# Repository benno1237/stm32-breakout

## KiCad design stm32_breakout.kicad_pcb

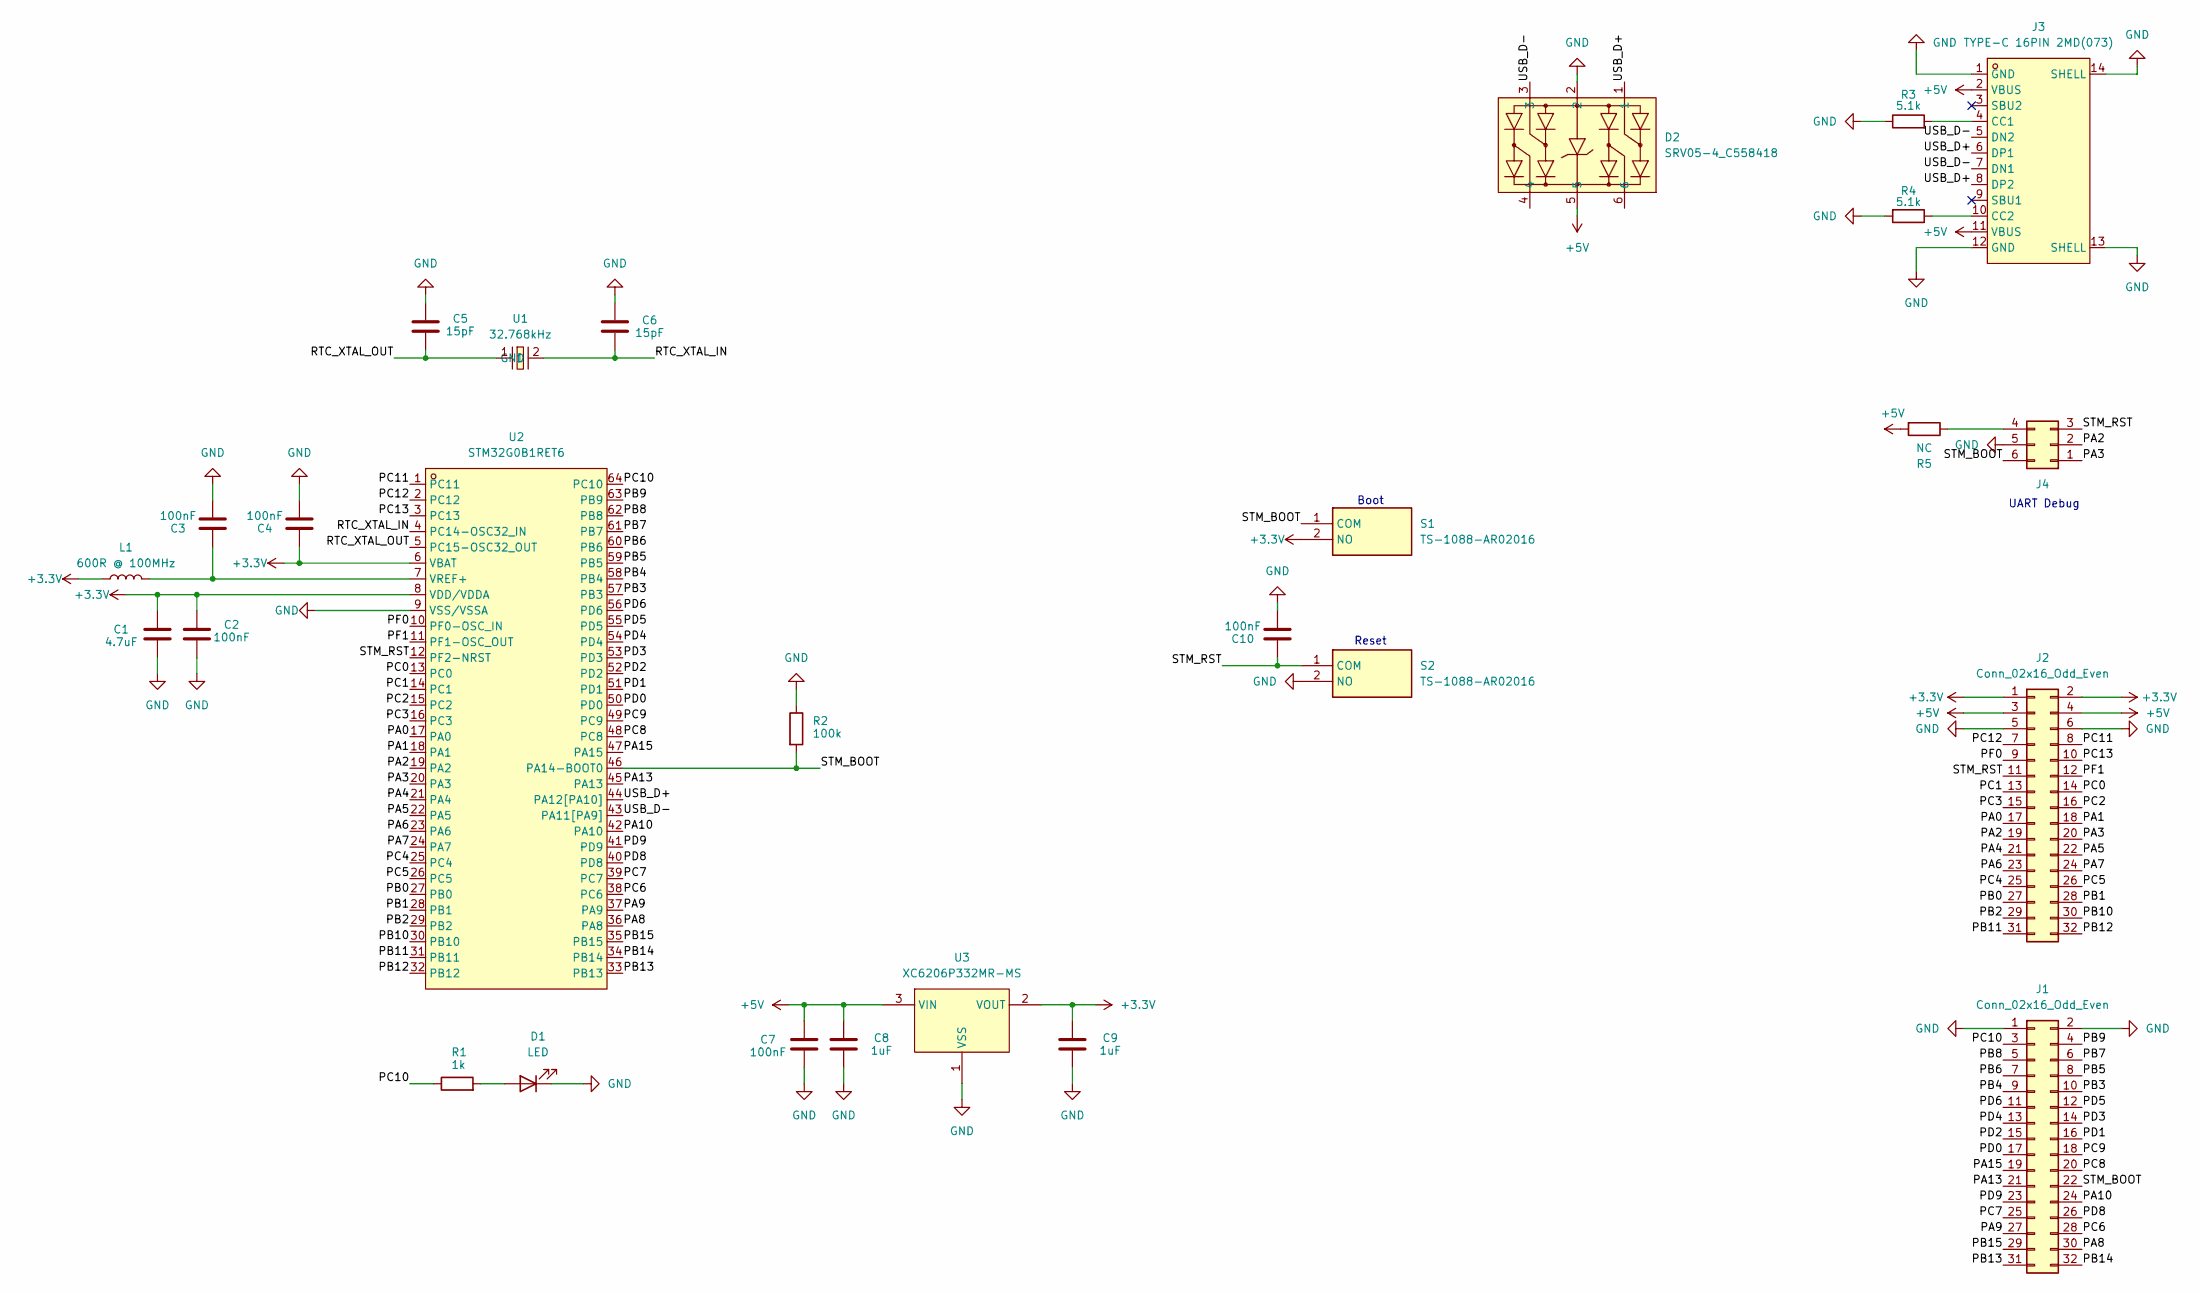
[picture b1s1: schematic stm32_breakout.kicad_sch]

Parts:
C1: 4.7uF; C_0603_1608Metric
C2, C3, C4, C7, C10: 100nF; C_0603_1608Metric
C5, C6: 15pF; C_0603_1608Metric
C8, C9: 1uF; C_0603_1608Metric
D1: LED; LED_0603_1608Metric
D2: SRV05-4_C558418; SOT-23-6_L2.9-W1.6-P0.95-LS2.8-BL; LCSC Part C558418
J1, J2: Conn_02x16_Odd_Even; PinHeader_2x16_P2.54mm_Vertical
J3: TYPE-C 16PIN 2MD(073); USB-C-SMD_TYPE-C-6PIN-2MD-073; LCSC Part C2765186
J4: PinSocket_2x03_P2.54mm_Vertical
L1: 600R @ 100MHz; L_0603_1608Metric
R1: 1k; R_0603_1608Metric
R2: 100k; R_0603_1608Metric
R3, R4: 5.1k; R_0603_1608Metric
R5: NC; R_0603_1608Metric
S1, S2: TS-1088-AR02016; SW-SMD_L3.9-W3.0-P4.45; Manufacturer_Part_Number TS-1088-AR02016
U1: 32.768kHz; CRYSTAL-SMD_L3.2-W1.5-1; LCSC Part C5361379
U2: STM32G0B1RET6; LQFP-64_L10.0-W10.0-P0.50-LS12.0-BL; LCSC Part C2829307
U3: XC6206P332MR-MS; SOT-23-3_L2.9-W1.3-P1.90-LS2.4-BR; LCSC Part C5252899

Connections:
+3.3V: C1.1, C2.1, C4.1, C9.2, J2.1, J2.2, L1.1, S1.2 (NO), U2.6 (VBAT), U2.8 (VDD/VDDA), U3.2 (VOUT)
+5V: C7.2, C8.2, D2.5, J2.3, J2.4, J3.2 (VBUS), J3.11 (VBUS), R5.2, U3.3 (VIN)
/PA0: J2.17, U2.17 (PA0)
/PA1: J2.18, U2.18 (PA1)
/PA2: J2.19, J4.2, U2.19 (PA2)
/PA3: J2.20, J4.1, U2.20 (PA3)
/PA4: J2.21, U2.21 (PA4)
/PA5: J2.22, U2.22 (PA5)
/PA6: J2.23, U2.23 (PA6)
/PA7: J2.24, U2.24 (PA7)
/PA8: J1.30, U2.36 (PA8)
/PA9: J1.27, U2.37 (PA9)
/PA10: J1.24, U2.42 (PA10)
/PA13: J1.21, U2.45 (PA13)
/PA15: J1.19, U2.47 (PA15)
/PB0: J2.27, U2.27 (PB0)
/PB1: J2.28, U2.28 (PB1)
/PB2: J2.29, U2.29 (PB2)
/PB3: J1.10, U2.57 (PB3)
/PB4: J1.9, U2.58 (PB4)
/PB5: J1.8, U2.59 (PB5)
/PB6: J1.7, U2.60 (PB6)
/PB7: J1.6, U2.61 (PB7)
/PB8: J1.5, U2.62 (PB8)
/PB9: J1.4, U2.63 (PB9)
/PB10: J2.30, U2.30 (PB10)
/PB11: J2.31, U2.31 (PB11)
/PB12: J2.32, U2.32 (PB12)
/PB13: J1.31, U2.33 (PB13)
/PB14: J1.32, U2.34 (PB14)
/PB15: J1.29, U2.35 (PB15)
/PC0: J2.14, U2.13 (PC0)
/PC1: J2.13, U2.14 (PC1)
/PC2: J2.16, U2.15 (PC2)
/PC3: J2.15, U2.16 (PC3)
/PC4: J2.25, U2.25 (PC4)
/PC5: J2.26, U2.26 (PC5)
/PC6: J1.28, U2.38 (PC6)
/PC7: J1.25, U2.39 (PC7)
/PC8: J1.20, U2.48 (PC8)
/PC9: J1.18, U2.49 (PC9)
/PC10: J1.3, R1.1, U2.64 (PC10)
/PC11: J2.8, U2.1 (PC11)
/PC12: J2.7, U2.2 (PC12)
/PC13: J2.10, U2.3 (PC13)
/PD0: J1.17, U2.50 (PD0)
/PD1: J1.16, U2.51 (PD1)
/PD2: J1.15, U2.52 (PD2)
/PD3: J1.14, U2.53 (PD3)
/PD4: J1.13, U2.54 (PD4)
/PD5: J1.12, U2.55 (PD5)
/PD6: J1.11, U2.56 (PD6)
/PD8: J1.26, U2.40 (PD8)
/PD9: J1.23, U2.41 (PD9)
/PF0: J2.9, U2.10 (PF0-OSC_IN)
/PF1: J2.12, U2.11 (PF1-OSC_OUT)
/RTC_XTAL_IN: C6.2, U1.2 (GND), U2.4 (PC14-OSC32_IN)
/RTC_XTAL_OUT: C5.2, U1.1, U2.5 (PC15-OSC32_OUT)
/STM_BOOT: J1.22, J4.6, R2.2, S1.1 (COM), U2.46 (PA14-BOOT0)
/STM_RST: C10.1, J2.11, J4.3, S2.1 (COM), U2.12 (PF2-NRST)
/USB_D+: D2.1, J3.6 (DP1), J3.8 (DP2), U2.44 (PA12[PA10])
/USB_D-: D2.3, J3.5 (DN2), J3.7 (DN1), U2.43 (PA11[PA9])
GND: C1.2, C2.2, C3.2, C4.2, C5.1, C6.1, C7.1, C8.1, C9.1, C10.2, D1.1 (K), D2.2, J1.1, J1.2, J2.5, J2.6, J3.1 (GND), J3.12 (GND), J3.13 (SHELL), J3.14 (SHELL), J4.5, R2.1, R3.1, R4.2, S2.2 (NO), U2.9 (VSS/VSSA), U3.1 (VSS)
unnamed: D1.2 (A), R1.2
unnamed: J3.4 (CC1), R3.2
unnamed: J3.10 (CC2), R4.1
unnamed: J4.4, R5.1
unnamed: C3.1, L1.2, U2.7 (VREF+)

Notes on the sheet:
Boot
Reset
UART Debug

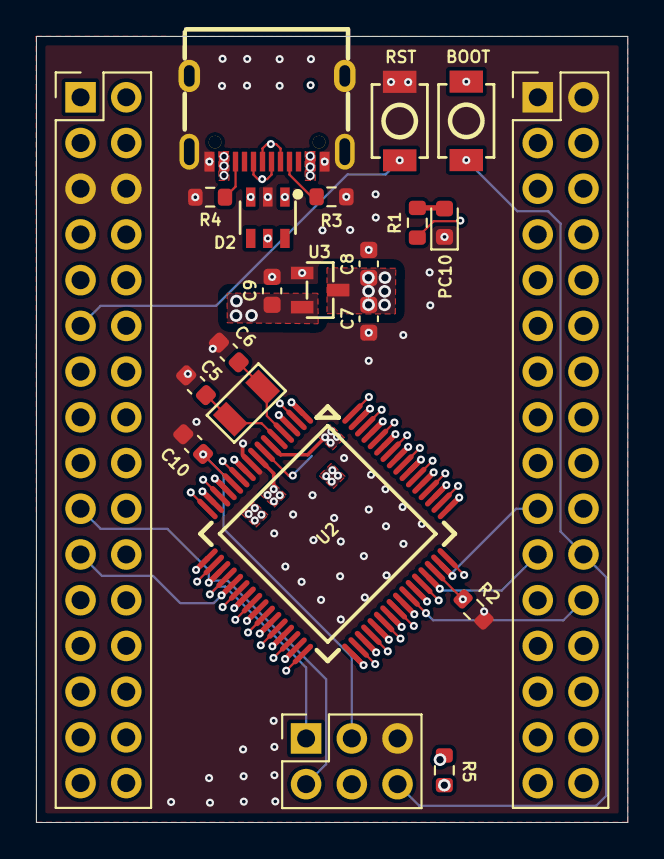
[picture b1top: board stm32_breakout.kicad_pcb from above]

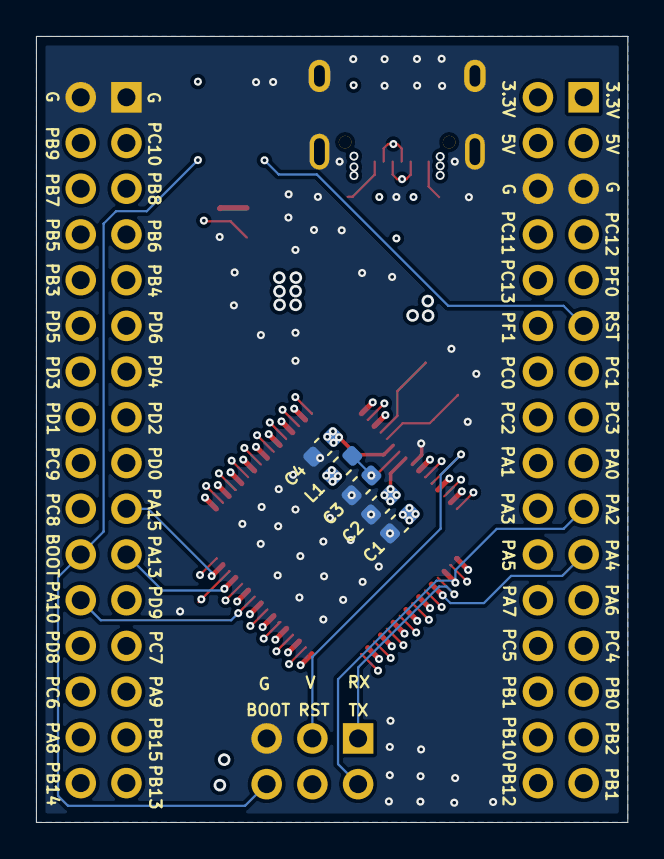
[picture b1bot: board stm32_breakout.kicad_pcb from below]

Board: 6 copper layers, 32.8 x 43.7 mm, 27 parts (5 on the bottom side), 68 nets.

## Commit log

2026-03-13 Initial commit: STM32 breakout board
2026-03-19 test framework
